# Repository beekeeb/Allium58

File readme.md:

# Allium58

The Allium58 is an open source 6*4+4keys column-staggered split keyboard. It is based on [Lily58 Pro created by kata0510](https://github.com/kata0510/Lily58/tree/master/Pro). The Allium58 shares the same layout as the Lily58 Pro and also supports using the original Lily58 Pro firmware. However, several changes have been made to the board:

- **Enhanced Wireless Capability:** The Allium58 is designed to be more suitable for wireless builds. It provides native support for utilizing power-saving nice!view or other memory-in-pixel displays. This allows for efficient power management and extended battery life.

- **Improved Battery Management:** To enhance battery management, power switches and JST battery sockets have been added to the Allium58. These additions make it easier to control power supply and facilitate seamless battery replacement.

- **GLP (Gateron Low Profile) Socket Compatibility:** A variant of Allium58 that works with Gateron Low Profile sockets. This allows for the use of Gateron KS-27/KS-33 low-profile key switches.

## Status

| Variant  | Status  |
| ------------ | ------------ |
| GLP (Gateron Low Profile) | Ready  |
| MX & Choc  | WIP  |

## Photos

## Bill of Materials (BOM)

### Required

| Name | Count | Remarks |
|:-|:-|:-|
| PCB | 1 set | |
| Top plate | 2 sheets | 1.2mm thick |
| Bottom plate / 3D printed case | 1 set | |
| OLED cover | 2 | |
| Pro Micro (compatible with Sea Picro RP2040) / nice!nano or equivalent | 2 |  |
| Reset button | 2 | TS-1136 THT |
| Diodes | 58 | SMD Only (SOD-123 Package) |
| Hotswap Sockets | 58 | [GLP variant] Gateron Low Profile Hotswap Sockets |
| Key switches | 58 | [GLP variant] Gateron KS-33 / KS-27 |
| Keycaps | 58 pieces | 1u 56 pcs, 1.5u 2 pcs [GLP Keycaps Comparison](https://showcase.beekeeb.com/the-keycaps-of-gateron-low-profile-key-switches-and-kailh-choc-v1-key-switch/) |
| Female Threaded Brass Spacer M2 5mm | 10 pieces | For Case assembly |
| Female Threaded Brass Spacer M2 9mm (or 14mm with MCU sockets) | 4 pieces | For OLED cover |
| GP823 Screw M2 4mm | 28 screws | |
| [Wired build] TRRS (4 poles) cable | 1 |  |
| [Wired build] TRRS jack | 2 |  |
| [Wired build] Micro USB or USB-C cable | 1 | Avoid charge-only cables |
| [Wireless build] JST battery socket | 2 | |
| [Wireless build] Battery with JST connector | 2 | |
| [Wireless build] Battery / power switch | 2 | IS-1290A-W-G / MSK12C02 / SSSS811101 |

### Optional

| Name | Count | Remarks |
|:-|:-|:-|
| OLED module / nice!view display | 2 | |
| Microcontroller / OLED Sockets & Pins | 1 set |  |

## Case
- Top Plate & Low Profile Bottom Case: https://www.printables.com/model/657755-low-profile-case-for-allium58-glp

## Firmware

- Wired: [QMK](https://github.com/qmk/qmk_firmware "QMK") - compatible with `lily58/rev1`
- Wired: [Vial](https://github.com/vial-kb/vial-qmk "Vial") (based on QMK) - supported
- Wireless: [ZMK](https://github.com/zmkfirmware/zmk "ZMK") - supported

## Ordering Parts

- Wired: https://shop.beekeeb.com/product/allium58-glp-wired-kit/
- Wireless: https://shop.beekeeb.com/product/allium58-glp-wireless-kit/

## External Libraries

* [https://github.com/siderakb/key-switches.pretty](https://github.com/siderakb/key-switches.pretty)
* [https://github.com/foostan/kbd](https://github.com/foostan/kbd)

## More Information

* [A great doc about Gateron Low Profile switches writen by Rafael Yumagulov](https://ergonautkb.github.io/docs/switches/gateron-low-profile/)
* [Keycaps for Gateron Low Profile Key Switches](https://showcase.beekeeb.com/the-keycaps-of-gateron-low-profile-key-switches-and-kailh-choc-v1-key-switch/)

## Credits

This open source hardware project is created by [beekeeb](https://beekeeb.shop) and other contributors. It is based on [Lily58 Pro created by kata0510](https://github.com/kata0510/Lily58/tree/master/Pro).

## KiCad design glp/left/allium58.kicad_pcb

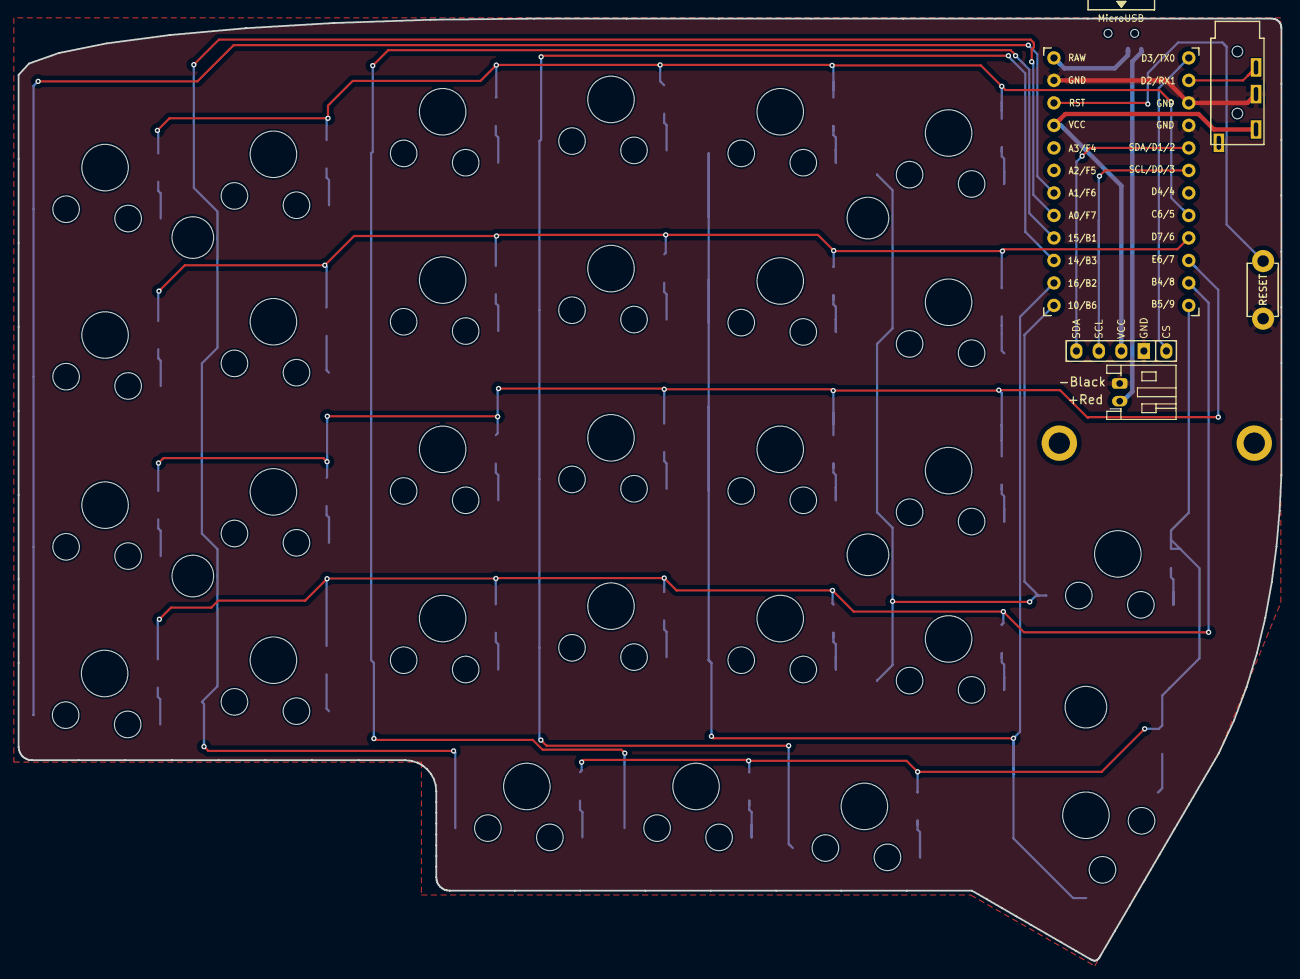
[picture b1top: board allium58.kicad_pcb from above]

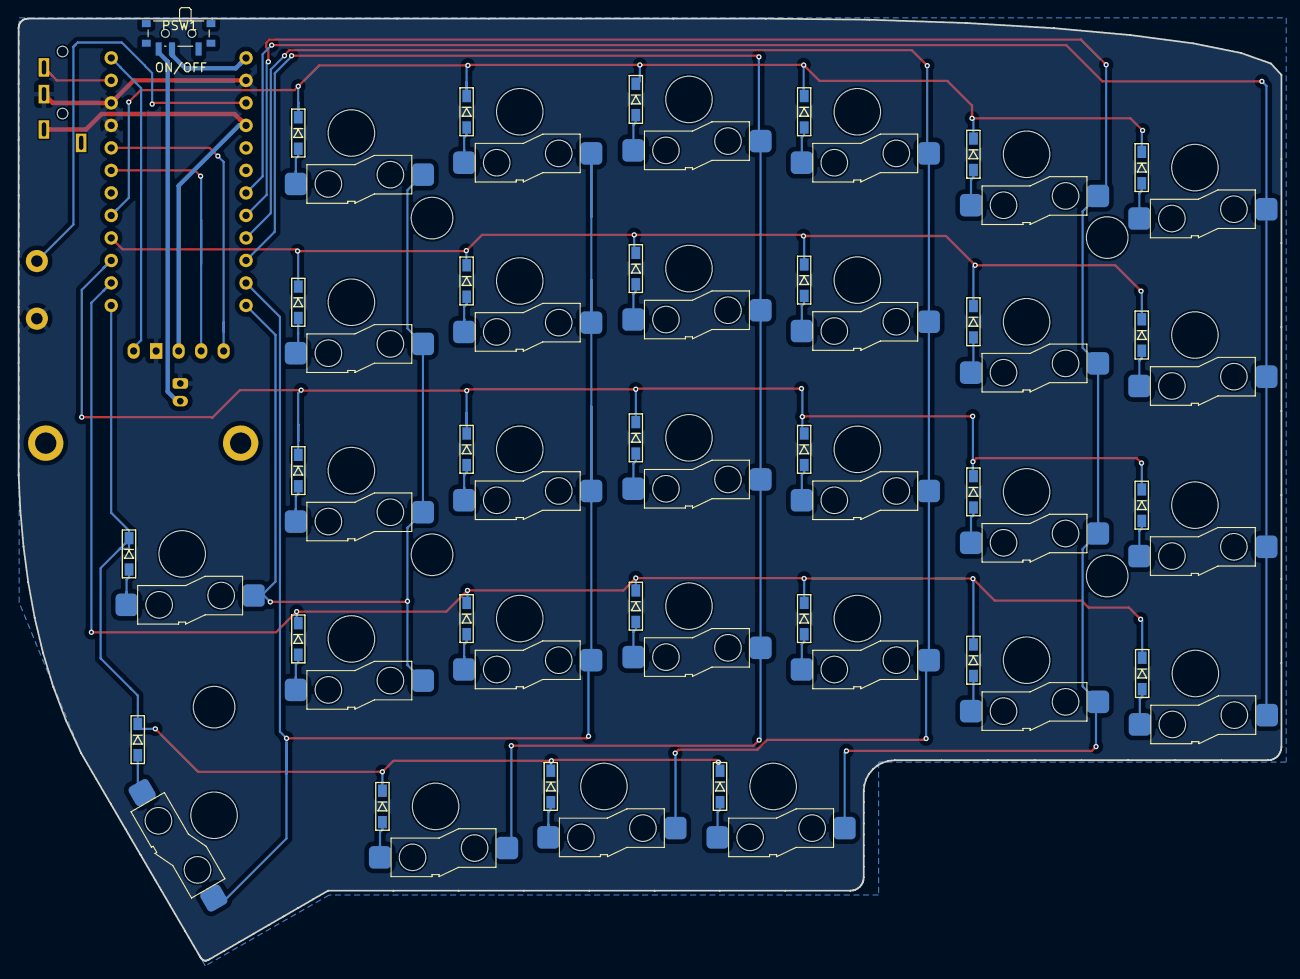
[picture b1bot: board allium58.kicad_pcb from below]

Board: 2 copper layers, 142.5 x 106.3 mm, 71 parts (37 on the bottom side), 49 nets.

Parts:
BATJ1: Conn_01x02_Female; JST_PH_S2B-PH-K_1x02_P2.00mm_Horizontal
D1, D2, D3, D4, D5, D6, D7, D8, D9, D10, D11, D12, D13, D14, D15, D16, D17, D18, D19, D20, D21, D22, D23, D24, D25, D26, D27, D28, D29: D; D3_SMD_v2
J2: 4PIN; MJ-4PP-9
J3: OLED; nice_view_1side
PSW1: SW_SPST; SW_SPDT_PCM12
RSW1: SW_RST; TACT_SWITCH_TVBP06
SW1, SW2, SW3, SW4, SW5, SW6, SW7, SW8, SW9, SW10, SW11, SW12, SW13, SW14, SW15, SW16, SW17, SW18, SW19, SW20, SW21, SW22, SW23, SW24, SW25, SW26, SW27, SW28, SW29: SW_PUSH; SW_Gateron_LowProfile_HotSwap
TH1, TH2: HOLE; M2_HOLE_PCB
TH3, TH4, TH5, TH6, TH7: HOLE; HOLE_M2_TH
U1: ProMicro; ProMicro_v3

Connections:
+BATT: BATJ1.1, PSW1.3 (C)
CS: J3.5, U1.1 (TX(PD3))
DATA: J2.3, U1.2 (RX(PD2))
GND: BATJ1.2, J2.2, J3.4, RSW1.1, U1.3 (GND), U1.4 (GND), U1.23 (GND)
unnamed: D1.2 (A), SW1.2
unnamed: D2.2 (A), SW2.2
unnamed: D3.2 (A), SW3.2
unnamed: D4.2 (A), SW4.2
unnamed: D5.2 (A), SW5.2
unnamed: D6.2 (A), SW6.2
unnamed: D7.2 (A), SW7.2
unnamed: D8.2 (A), SW8.2
unnamed: D9.2 (A), SW9.2
unnamed: D10.2 (A), SW10.2
unnamed: D11.2 (A), SW11.2
unnamed: D12.2 (A), SW12.2
unnamed: D13.2 (A), SW13.2
unnamed: D14.2 (A), SW14.2
unnamed: D15.2 (A), SW15.2
unnamed: D16.2 (A), SW16.2
unnamed: D17.2 (A), SW17.2
unnamed: D18.2 (A), SW18.2
unnamed: D19.2 (A), SW19.2
unnamed: D20.2 (A), SW20.2
unnamed: D21.2 (A), SW21.2
unnamed: D22.2 (A), SW22.2
unnamed: D23.2 (A), SW23.2
unnamed: D24.2 (A), SW24.2
unnamed: D25.2 (A), SW25.2
unnamed: D26.2 (A), SW26.2
unnamed: D27.2 (A), SW27.2
unnamed: D28.2 (A), SW28.2
unnamed: D29.2 (A), SW29.2
RESET: RSW1.2, U1.22 (RST)
SCL: J3.2, U1.6 (SCL(PD0))
SDA: J3.1, U1.5 (SDA(PD1))
VCC: J2.1, J3.3, U1.21 (VCC)
col0: SW6.1, SW12.1, SW18.1, SW24.1, U1.18 (A1(PF6))
col1: SW5.1, SW11.1, SW17.1, SW23.1, SW29.1, U1.17 (A0(PF7))
col2: SW4.1, SW10.1, SW16.1, SW22.1, SW28.1, U1.16 (D15(PB1))
col3: SW3.1, SW9.1, SW15.1, SW21.1, SW27.1, U1.15 (D14(PB3))
col4: SW2.1, SW8.1, SW14.1, SW20.1, SW26.1, U1.14 (D16(PB2))
col5: SW1.1, SW7.1, SW13.1, SW19.1, SW25.1, U1.13 (D10(PB6))
raw: PSW1.2 (B), U1.24 (RAW)
row0: D1.1 (K), D2.1 (K), D3.1 (K), D4.1 (K), D5.1 (K), D6.1 (K), U1.8 (D5(PC6))
row1: D7.1 (K), D8.1 (K), D9.1 (K), D10.1 (K), D11.1 (K), D12.1 (K), U1.9 (D6(PD7))
row2: D13.1 (K), D14.1 (K), D15.1 (K), D16.1 (K), D17.1 (K), D18.1 (K), U1.10 (D7(PE6))
row3: D19.1 (K), D20.1 (K), D21.1 (K), D22.1 (K), D23.1 (K), D24.1 (K), U1.11 (D8(PB4))
row4: D25.1 (K), D26.1 (K), D27.1 (K), D28.1 (K), D29.1 (K), U1.12 (D9(PB5))

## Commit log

2023-11-16 Add readme
2023-11-16 Add LICENSE
2023-11-24 Add links to case files
2023-11-24 Fix typo
2024-06-29 It's a tiny detail.
2025-06-10 Added battery- / power switch Added part numbers for reset button and battery- / power switch

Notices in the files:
readme.md:
License: MIT
